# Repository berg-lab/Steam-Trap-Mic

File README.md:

# Franklin Energy Steam Project - Stream Trap Monitor Firmware

## Overview
We are building a device which will monitor ultrasonic auditory data of steam traps involved with heating systems. Upon completion, the goal of this device is to be able to recognize what a failing steam trap sounds like, and broadcast an alert when a fault is detected. By catching these faults early on, we can save energy that would otherwise be wasted through silent, incorrect temperature regulation caused by the broken piece. This repo itself holds the firmware for this steam trap accessory, along with some test files and schematics of the accessory itself.

## Navigation
- **[firmware](firmware/)** - directory for all source files of the device firmware, as well as some test files.
- **[py](py/)** - directory for all python helper scripts, such as reading and processing serial data.
- **[schematic](schematic/)** - directory for visual documentation on the device's custom board design.

## Contributing
For contributing to the source code of this project, please create your own branch and use a pull request to get these changes onto the main branch. To begin development of your own local branch, run the following git CLI commands from terminal:
```
git clone https://github.com/berg-lab/Steam-Trap-Mic.git
cd Steam-Trap-Mic
git checkout -b your_branch_name
```
From here, you can make local changes to your branch and experiment with different code. Once the repo is in a good state to save and checkpoint, add all of your changes into a commit and push them to your branch on the remote repository:
```
git add .
git commit -m "commit message describing changes here"
git push -u origin your_branch_name
```
These new changes will now be visible to everyone with access to the repo on the web. This process should be done any time a significant change is made! _Note: the -u flag sets the designated push location as the default for the current local branch, so any subsequent pushes can be done with just the command_ `git push`.

To get your changes onto the main branch, please use a pull request. **AVOID PUSHING DIRECTLY TO MAIN.** You can open a pull request on Github by going to the "Pull requests" tab in the repo and clicking "New pull request." From here, select "main" for base and your branch for compare. Making sure all merge conflicts are resolved, and click "Create pull request." Once this pull request is reviewed, it can be merged to the main branch of production.

Lastly, because there are multiple people working on the repository, there will be changes made to main often, which need to be reflected on your local branch. You can bring these new changes onto your branch with one command: `git pull`. **ALWAYS PULL BEFORE YOU PUSH.** This will avoid merge conflicts which can occur if your pull requests do not contain the most recent changes made to main.

## Deployment
To upload the firmware onto the device, make sure it is connected to your computer through a COM port. In the Arduino IDE, open the project and select this port, which should be labeled with "Moteino M0" under `Tools > Port`. Finally, click "Upload" to transfer the code to the device and begin running the main loop.

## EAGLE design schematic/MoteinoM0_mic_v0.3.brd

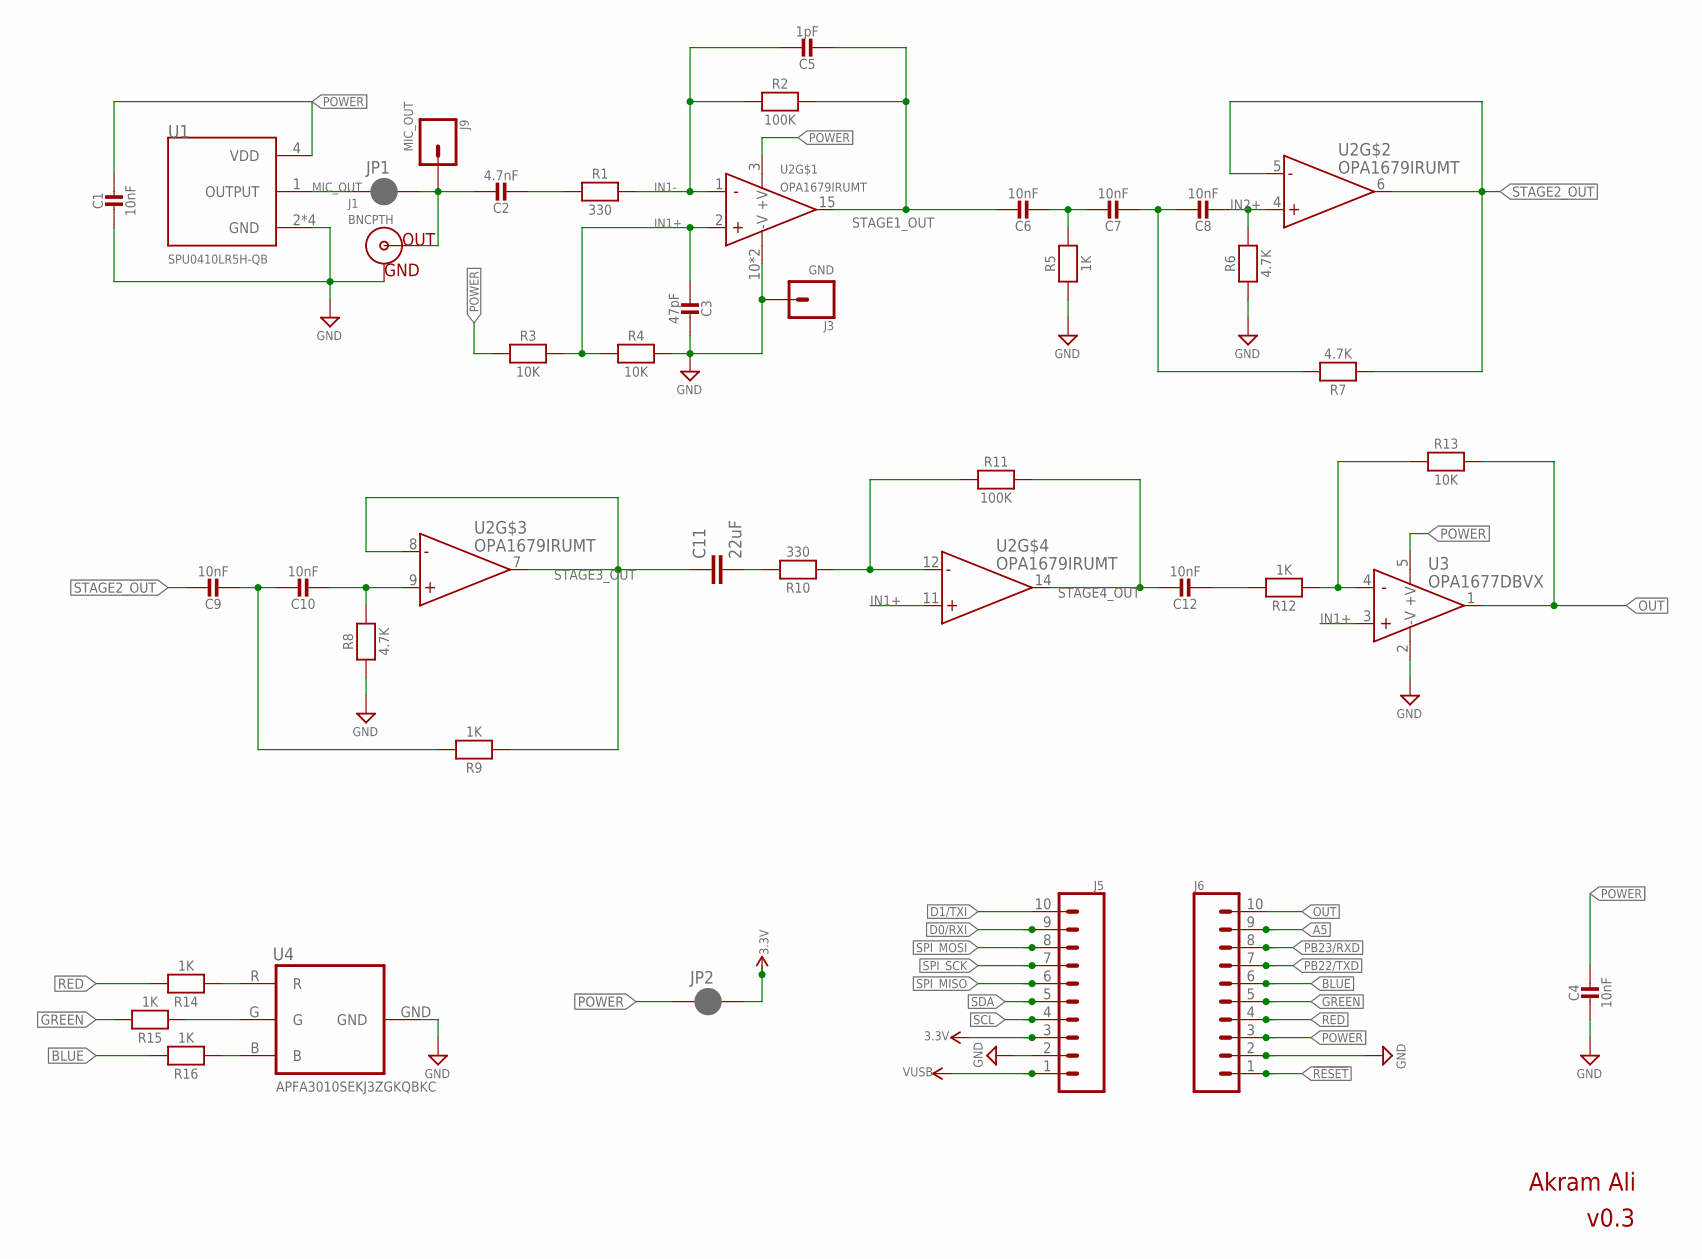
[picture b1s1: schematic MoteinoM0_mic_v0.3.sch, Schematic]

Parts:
C1, C4, C6, C7, C8, C9, C10, C12: 10nF; MICROBUILDER__0402MP; MPN GRM155R71H104KE14J
C2: 4.7nF; MICROBUILDER__0402MP; MPN GRM155R71H104KE14J
C3: 47pF; MICROBUILDER__0402MP; MPN GRM155R71H104KE14J
C5: 1pF; MICROBUILDER__0402MP; MPN GRM155R71H104KE14J
C11: 22uF; 0805
J1: BNCPTH; BNC
J3: GND; 1X01
J5, J6: CONN_10NO_SILK_PTH_FEMALE; 1X10_NO_SILK
J9: MIC_OUT; 1X01
JP1, JP2: JUMPER-SMT_2_NC_PASTE_SILK; SMT-JUMPER_2_NC_PASTE_SILK
R1, R10: 330; MICROBUILDER__0402MP; MPN RC0402FR-074K7P
R2, R11: 100K; MICROBUILDER__0402MP; MPN RC0402FR-074K7P
R3, R4, R13: 10K; MICROBUILDER__0402MP; MPN RC0402FR-074K7P
R5, R9, R12, R14, R15, R16: 1K; MICROBUILDER__0402MP; MPN RC0402FR-074K7P
R6, R7, R8: 4.7K; MICROBUILDER__0402MP; MPN RC0402FR-074K7P
U1: SPU0410LR5H-QB; XDCR_SPU0410LR5H-QB
U2: OPA1679IRUMT; QFN65P400X400X80-17N
U3: OPA1677DBVX; SOT23-5
U4: APFA3010SEKJ3ZGKQBKC; SMD-RA-4

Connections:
3.3V: J5.3, JP2.2
!RESET: J6.1
A5: J6.9
BLUE: J6.6, R16.2
D0/RXI: J5.9
D1/TXI: J5.10
GND: C1.2, C3.1, C4.2, J1.GND, J3.1, J5.2, J6.2, R4.2, R5.1, R6.1, R8.1, U1.2 (GND), U1.3 (GND), U1.5 (GND), U1.6 (GND), U2.10 (-V), U2.17 (-V), U3.2 (-V), U4.GND
GREEN: J6.5, R15.2
IN1+: C3.2, R3.2, R4.1, U2.2 (+IN), U2.11 (+IN), U3.3 (+IN)
IN1-: C5.1, R1.2, R2.1, U2.1 (-IN)
IN2+: C8.2, R6.2, U2.4 (+IN)
MIC_OUT: C2.1, J1.S (OUT), J9.1, JP1.2
unnamed: C9.2, C10.1, R9.2
unnamed: C6.2, C7.1, R5.2
unnamed: C7.2, C8.1, R7.2
unnamed: C2.2, R1.1
unnamed: R14.1, U4.R
unnamed: C10.2, R8.2, U2.9 (+IN)
unnamed: C11.2, R10.2
unnamed: R15.1, U4.G
unnamed: R10.1, R11.1, U2.12 (-IN)
unnamed: R16.1, U4.B
unnamed: C12.2, R12.2
unnamed: R12.1, R13.1, U3.4 (-IN)
unnamed: JP1.1, U1.1 (OUTPUT)
OUT: J6.10, R13.2, U3.1 (OUT)
PB22/TXD: J6.7
PB23/RXD: J6.8
POWER: C1.1, C4.1, J6.3, JP2.1, R3.1, U1.4 (VDD), U2.3 (+V), U3.5 (+V)
RED: J6.4, R14.2
SCL: J5.4
SDA: J5.5
SPI_MISO: J5.6
SPI_MOSI: J5.8
SPI_SCK: J5.7
STAGE1_OUT: C5.2, C6.1, R2.2, U2.15 (OUT)
STAGE2_OUT: C9.1, R7.1, U2.5 (-IN), U2.6 (OUT)
STAGE3_OUT: C11.1, R9.1, U2.7 (OUT), U2.8 (-IN)
STAGE4_OUT: C12.1, R11.2, U2.14 (OUT)
VUSB: J5.1

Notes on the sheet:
v0.3
Akram Ali

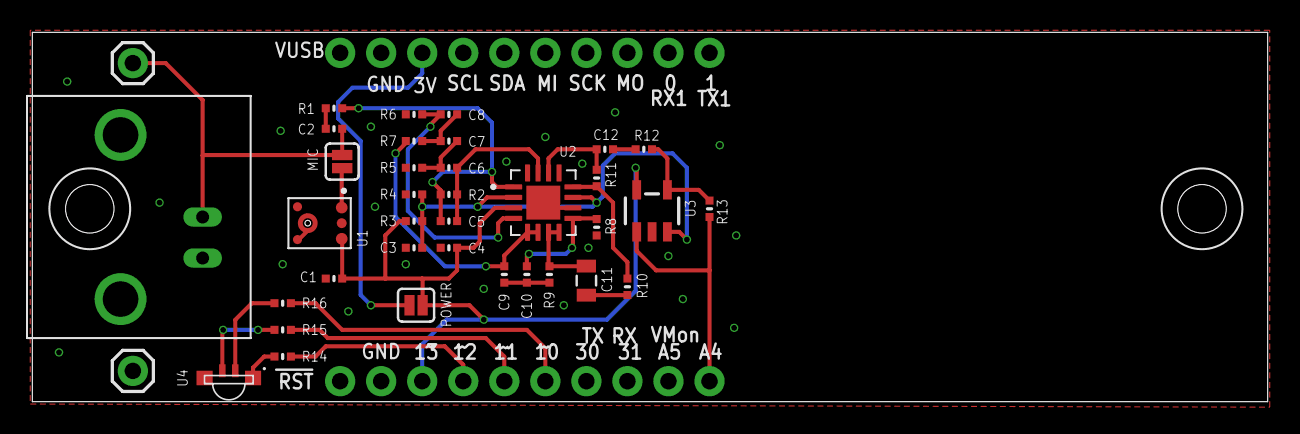
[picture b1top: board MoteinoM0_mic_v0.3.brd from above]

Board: 2 copper layers, 76.4 x 22.9 mm, 39 parts (0 on the bottom side), 28 nets.

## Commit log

2022-09-27 copying over from borc repo
2022-09-29 adding schematic illustrations
2022-10-05 firmware: adding starter files
2022-10-05 test: adding sweep test and py script to read from serial
2022-10-05 docs: adding readme
2022-10-10 config: fixing microphone pin
2022-10-10 py: changing usage to be parameter based
2022-10-11 doc: adding section for contributing on readme
2023-06-02 updating helper scripts
2023-06-02 syncing recent changes to firmware and serial_reader
2023-06-02 renaming sweep to serial
2023-06-02 removing serial test
2023-06-02 updating documentation
2023-06-02 common.h: adding some global constants
2023-06-02 fixing serial port malfunction on win 10
2023-06-02 starting firmware testing implementation
2023-06-02 common: cleaning up unnecessary config from borc
2023-06-02 small edits to radio.c/.h
2023-06-02 uploading files, version compiles but remains untested
2023-06-02 common.h and firmware.ino: removing unnecessary stuff and adding small macros
2023-06-02 cleaning up experimental file micRead.cpp
2023-08-21 Eduardos first commit
2023-08-24 Updating the steam trap code to include new data.
2023-08-25 updated code for temperature version
2023-08-28 fixed class methods and added serial print statements
2023-09-05 added Test3 folder as well as changed some lines of firmware.ino
2023-09-13 modified radio code implementing Test3.ino features
2023-09-18 Working radio!
2023-09-18 implemented thermistor with radio
2023-09-22 converting float to uint16_t for radio send
2023-10-13 small change to pins
2023-10-13 Modified code for sleeping 10 mins.
2023-10-13 ammending issue from previous commit
2023-10-19 updating radio format and event blinking patterns
2023-10-19 defining max value for the ADC
2023-10-19 fixing function signatures
2023-10-19 fixing C errors in timer function
2023-10-19 fixing some syntax errs in firmware
2023-10-28 fixing timer discrepancy
2023-10-28 removing Test3

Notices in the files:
parts and their libraries:
SparkFun-Connectors: Licensing: Creative Commons ShareAlike 4.0 International - https://creativecommons.org/licenses/by-sa/4.0
